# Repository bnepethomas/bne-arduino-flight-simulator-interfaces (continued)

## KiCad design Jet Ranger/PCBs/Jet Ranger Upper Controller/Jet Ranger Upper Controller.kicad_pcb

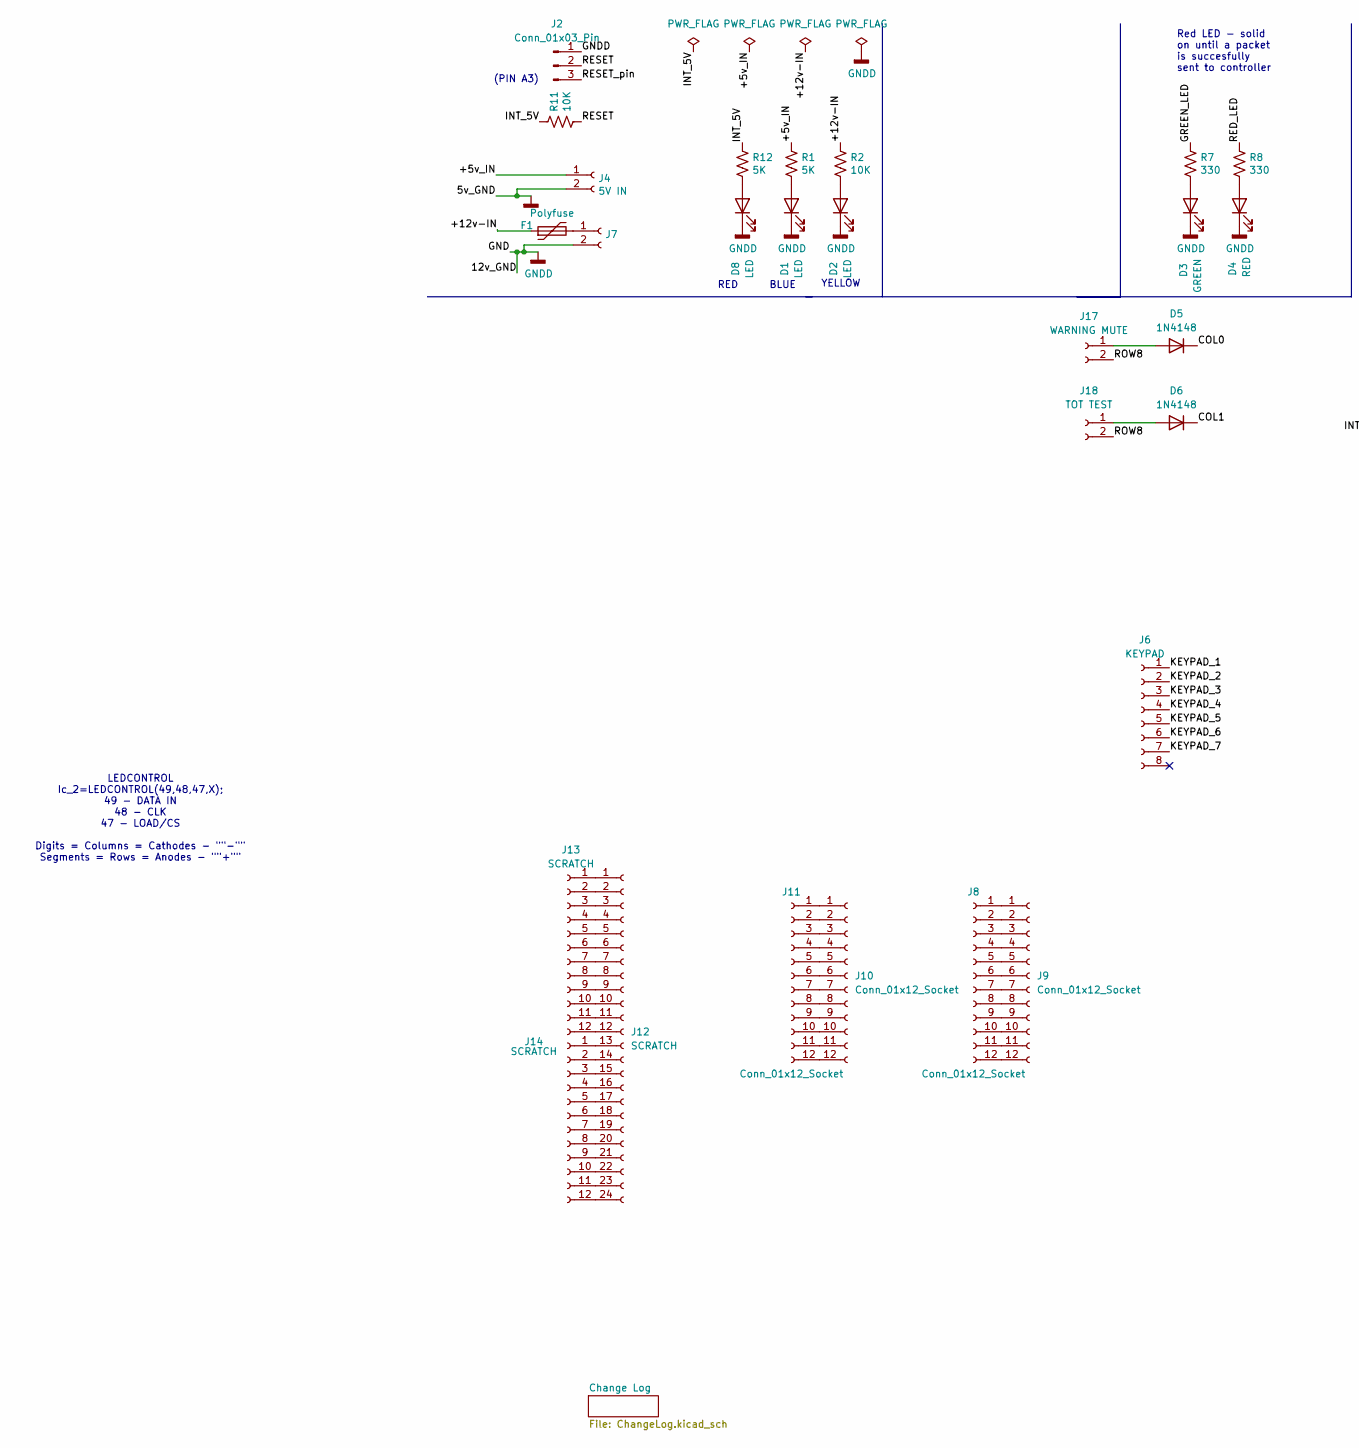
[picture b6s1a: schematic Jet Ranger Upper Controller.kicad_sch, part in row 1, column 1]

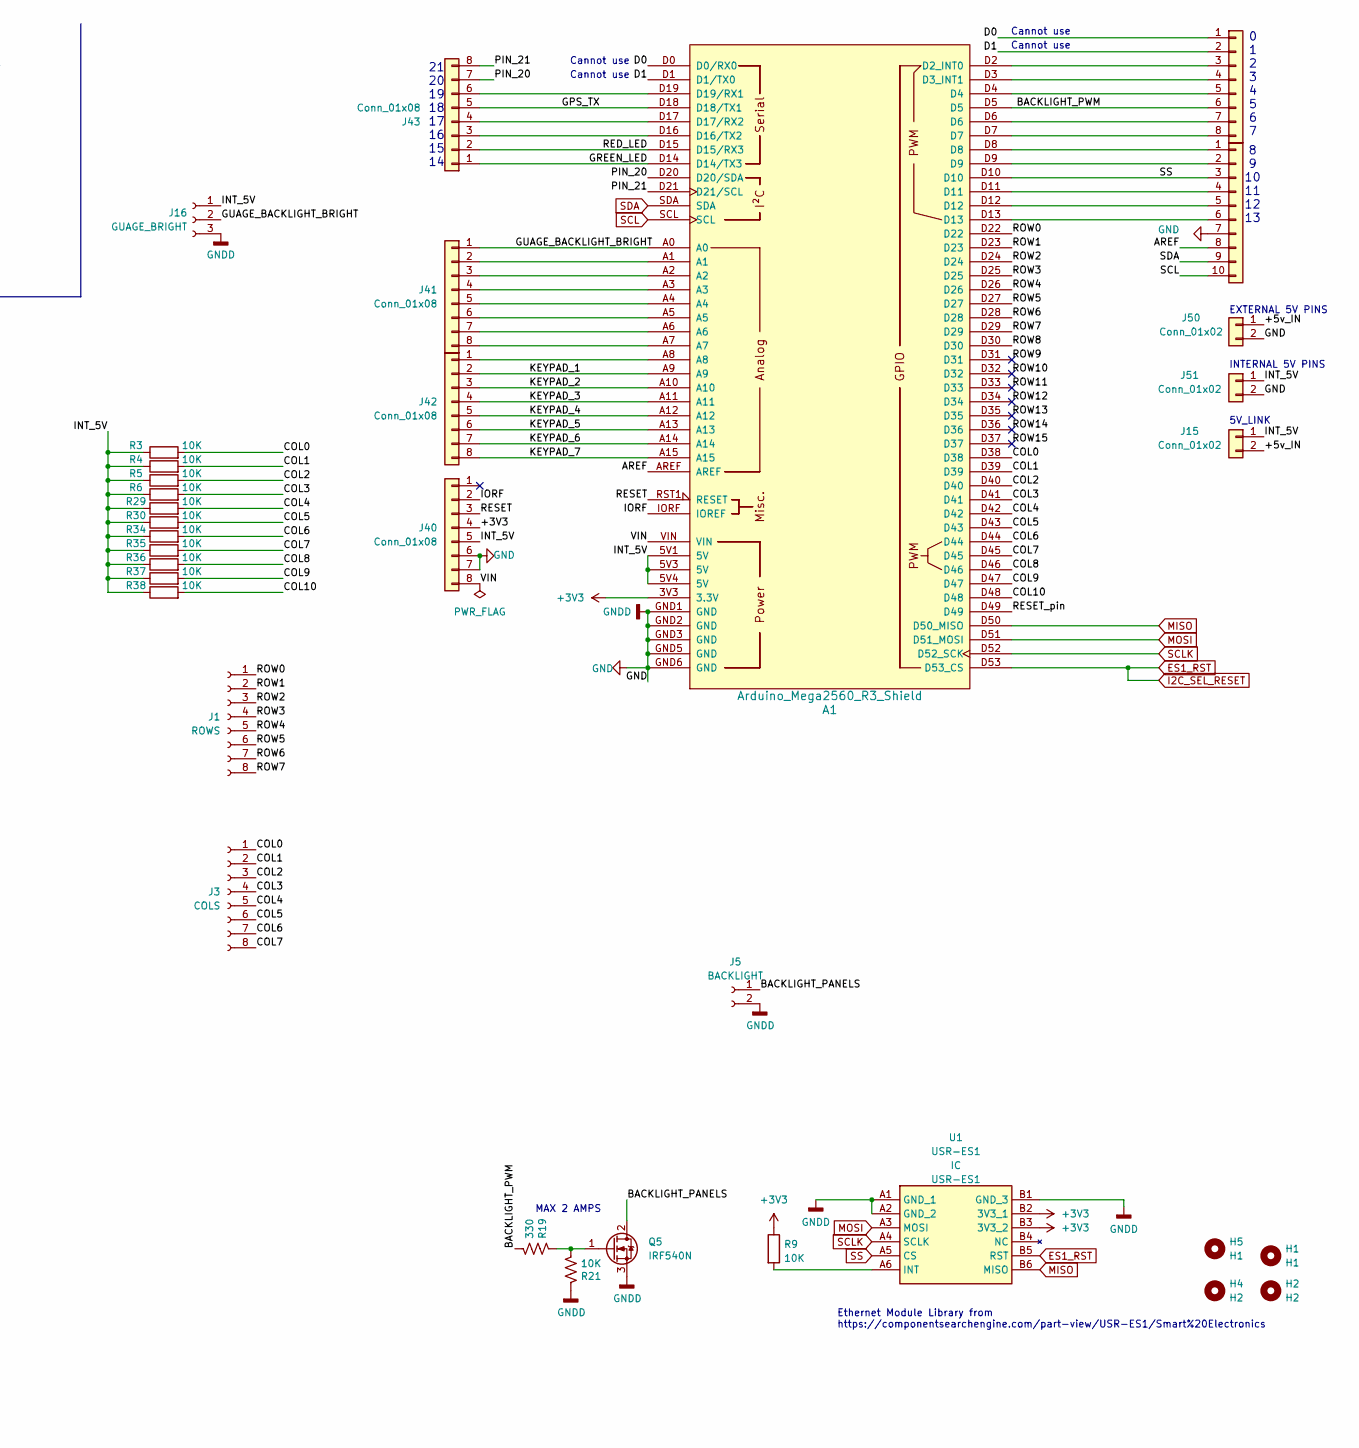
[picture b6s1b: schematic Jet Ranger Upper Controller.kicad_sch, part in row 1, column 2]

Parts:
A1: Arduino_Mega2560_R3_Shield
D1, D2, D8: LED; LED_D3.0mm
D3: GREEN; LED_D3.0mm
D4: RED; LED_D3.0mm
D5, D6: 1N4148; D_DO-35_SOD27_P7.62mm_Horizontal
F1: Polyfuse; Fuse_Bourns_MF-RG400
H1, H5: H1; MountingHole_3.2mm_M3
H2, H4: H2; MountingHole_3.2mm_M3
J1: ROWS; Molex_KK-254_AE-6410-08A_1x08_P2.54mm_Vertical
J2: Conn_01x03_Pin; PinHeader_1x03_P2.54mm_Vertical
J3: COLS; Molex_KK-254_AE-6410-08A_1x08_P2.54mm_Vertical
J4: 5V IN; BarrelJack_Horizontal
J5: BACKLIGHT; Molex_KK-254_AE-6410-02A_1x02_P2.54mm_Vertical
J6: KEYPAD; Molex_KK-254_AE-6410-08A_1x08_P2.54mm_Vertical
J7: STEPPER IN 12-20VDC; BarrelJack_Horizontal
J8, J9, J10, J11: Conn_01x12_Socket; PinHeader_1x12_P2.54mm_Vertical
J12: SCRATCH; IDC-Header_2x12_P2.54mm_Vertical
J13, J14: SCRATCH; PinHeader_1x12_P2.54mm_Vertical
J15, J50, J51: Conn_01x02; PinHeader_1x02_P2.54mm_Vertical
J16: GUAGE_BRIGHT; Molex_KK-254_AE-6410-03A_1x03_P2.54mm_Vertical
J17: WARNING MUTE; Molex_KK-254_AE-6410-02A_1x02_P2.54mm_Vertical
J18: TOT TEST; Molex_KK-254_AE-6410-02A_1x02_P2.54mm_Vertical
J40, J41, J42, J43, J44: Conn_01x08; PinHeader_1x08_P2.54mm_Vertical
J45: Conn_01x10; PinHeader_1x10_P2.54mm_Vertical
Q5: IRF540N; TO-220-3_Vertical
R1, R12: 5K; R_Axial_DIN0207_L6.3mm_D2.5mm_P2.54mm_Vertical
R2, R3, R4, R5, R6, R9, R11, R21, R29, R30, R34, R35, R36, R37, R38: 10K; R_Axial_DIN0207_L6.3mm_D2.5mm_P2.54mm_Vertical
R7, R8, R19: 330; R_Axial_DIN0207_L6.3mm_D2.5mm_P2.54mm_Vertical
U1: USR-ES1; USRES1; Manufacturer_Part_Number USR-ES1

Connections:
+3V3: A1.3V3 (3.3V), J40.4, R9.1, U1.B2 (3V3_1), U1.B3 (3V3_2)
/+5v_IN: J4.1, J15.2, J50.1, R1.1
/+12v-IN: F1.1, R2.1
/AREF: A1.AREF, J45.8
/BACKLIGHT_PANELS: J5.1, Q5.2 (D)
/BACKLIGHT_PWM: A1.D5, J44.6, R19.2
/COL0: A1.D38, D5.1 (K), J3.1, R3.2
/COL1: A1.D39, D6.1 (K), J3.2, R4.2
/COL2: A1.D40, J3.3, R5.2
/COL3: A1.D41, J3.4, R6.2
/COL4: A1.D42, J3.5, R29.2
/COL5: A1.D43, J3.6, R30.2
/COL6: A1.D44, J3.7, R34.2
/COL7: A1.D45, J3.8, R35.2
/COL8: A1.D46, R36.2
/COL9: A1.D47, R37.2
/COL10: A1.D48, R38.2
/D0: A1.D0 (D0/RX0), J44.1
/D1: A1.D1 (D1/TX0), J44.2
/GPS_TX: A1.D18 (D18/TX1), J43.5
/GREEN_LED: A1.D14 (D14/TX3), J43.1, R7.1
/GUAGE_BACKLIGHT_BRIGHT: A1.A0, J16.2, J41.1
/INT_5V: A1.5V1 (5V), A1.5V3 (5V), A1.5V4 (5V), J15.1, J16.1, J40.5, J51.1, R3.1, R4.1, R5.1, R6.1, R11.1, R12.1, R29.1, R30.1, R34.1, R35.1, R36.1, R37.1, R38.1
/IORF: A1.IORF (IOREF), J40.2
/KEYPAD_1: A1.A9, J6.1, J42.2
/KEYPAD_2: A1.A10, J6.2, J42.3
/KEYPAD_3: A1.A11, J6.3, J42.4
/KEYPAD_4: A1.A12, J6.4, J42.5
/KEYPAD_5: A1.A13, J6.5, J42.6
/KEYPAD_6: A1.A14, J6.6, J42.7
/KEYPAD_7: A1.A15, J6.7, J42.8
/PIN_20: A1.D20 (D20/SDA), J43.7
/PIN_21: A1.D21 (D21/SCL), J43.8
/RED_LED: A1.D15 (D15/RX3), J43.2, R8.1
/RESET: A1.RST1 (RESET), J2.2, J40.3, R11.2
/RESET_pin: A1.D49, J2.3
/ROW0: A1.D22, J1.1
/ROW1: A1.D23, J1.2
/ROW2: A1.D24, J1.3
/ROW3: A1.D25, J1.4
/ROW4: A1.D26, J1.5
/ROW5: A1.D27, J1.6
/ROW6: A1.D28, J1.7
/ROW7: A1.D29, J1.8
/ROW8: A1.D30, J17.2, J18.2
/ROW9: A1.D31
/ROW10: A1.D32
/ROW11: A1.D33
/ROW12: A1.D34
/ROW13: A1.D35
/ROW14: A1.D36
/ROW15: A1.D37
/VIN: A1.VIN, J40.8
ES1_RST: A1.D53 (D53_CS), U1.B5 (RST)
GND: A1.GND1 (GND), A1.GND2 (GND), A1.GND3 (GND), A1.GND5 (GND), A1.GND6 (GND), D1.1 (K), D2.1 (K), D3.1 (K), D4.1 (K), D8.1 (K), J2.1, J4.2, J5.2, J7.2, J16.3, J40.6, J40.7, J45.7, J50.2, J51.2, Q5.3 (S), R21.1, U1.A1 (GND_1), U1.A2 (GND_2), U1.B1 (GND_3)
MISO: A1.D50 (D50_MISO), U1.B6 (MISO)
MOSI: A1.D51 (D51_MOSI), U1.A3 (MOSI)
unnamed: A1.D2 (D2_INT0), J44.3
unnamed: A1.D3 (D3_INT1), J44.4
unnamed: A1.D16 (D16/TX2), J43.3
unnamed: A1.D17 (D17/RX2), J43.4
unnamed: A1.D19 (D19/RX1), J43.6
unnamed: D1.2 (A), R1.2
unnamed: D2.2 (A), R2.2
unnamed: D3.2 (A), R7.2
unnamed: D4.2 (A), R8.2
unnamed: D5.2 (A), J17.1
unnamed: D6.2 (A), J18.1
unnamed: D8.2 (A), R12.2
unnamed: F1.2, J7.1
unnamed: J8.1, J9.1
unnamed: J8.2, J9.2
unnamed: J8.3, J9.3
unnamed: J8.4, J9.4
unnamed: J8.5, J9.5
unnamed: J8.6, J9.6
unnamed: J8.7, J9.7
unnamed: J8.8, J9.8
unnamed: J8.9, J9.9
unnamed: J8.10, J9.10
unnamed: J8.11, J9.11
unnamed: J8.12, J9.12
unnamed: J10.1, J11.1
unnamed: J10.2, J11.2
unnamed: J10.3, J11.3
unnamed: J10.4, J11.4
unnamed: J10.5, J11.5
unnamed: J10.6, J11.6
unnamed: J10.7, J11.7
unnamed: J10.8, J11.8
unnamed: J10.9, J11.9
unnamed: J10.10, J11.10
unnamed: J10.11, J11.11
unnamed: J10.12, J11.12
unnamed: J12.1, J13.1
unnamed: J12.2, J13.2
unnamed: J12.3, J13.3
unnamed: J12.4, J13.4
unnamed: J12.5, J13.5
unnamed: J12.6, J13.6
unnamed: J12.7, J13.7
unnamed: J12.8, J13.8
unnamed: J12.9, J13.9
unnamed: J12.10, J13.10
unnamed: J12.11, J13.11
unnamed: J12.12, J13.12
unnamed: J12.13, J14.1
unnamed: J12.14, J14.2
unnamed: J12.15, J14.3
unnamed: J12.16, J14.4
unnamed: J12.17, J14.5
unnamed: J12.18, J14.6
unnamed: J12.19, J14.7
unnamed: J12.20, J14.8
unnamed: J12.21, J14.9
unnamed: J12.22, J14.10
unnamed: J12.23, J14.11
unnamed: J12.24, J14.12
unnamed: A1.A1, J41.2
unnamed: A1.A2, J41.3
unnamed: A1.A3, J41.4
unnamed: A1.A4, J41.5
unnamed: A1.A5, J41.6
unnamed: A1.A6, J41.7
unnamed: A1.A7, J41.8
unnamed: A1.A8, J42.1
unnamed: A1.D4, J44.5
unnamed: A1.D6, J44.7
unnamed: A1.D7, J44.8
unnamed: A1.D8, J45.1
unnamed: A1.D9, J45.2
unnamed: A1.D11, J45.4
unnamed: A1.D12, J45.5
unnamed: A1.D13, J45.6
unnamed: Q5.1 (G), R19.1, R21.2
unnamed: R9.2, U1.A6 (INT)
SCL: A1.SCL, J45.10
SCLK: A1.D52 (D52_SCK), U1.A4 (SCLK)
SDA: A1.SDA, J45.9
SS: A1.D10, J45.3, U1.A5 (CS)

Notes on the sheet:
YELLOW
MAX 2 AMPS
BLUE
INTERNAL 5V PINS
Ethernet Module Library from https://componentsearchengine.com/part-view/USR-ES1/Smart%20Electronics
Cannot use
RED
(PIN A3)
0 1 2 3 4 5 6 7
LEDCONTROL Ic_2=LEDCONTROL(49,48,47,X); 49 - DATA IN 48 - CLK 47 - LOAD/CS Digits = Columns = Cathodes - ""-"" Segments = Rows = Anodes - ""+""
Red LED - solid on until a packet is succesfully sent to controller
5V_LINK
21 20 19 18 17 16 15 14
EXTERNAL 5V PINS
8 9 10 11 12 13

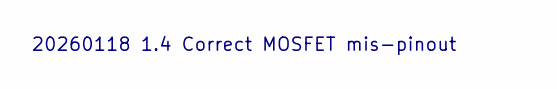
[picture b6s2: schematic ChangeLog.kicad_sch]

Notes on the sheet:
20260118 1.4 Correct MOSFET mis-pinout

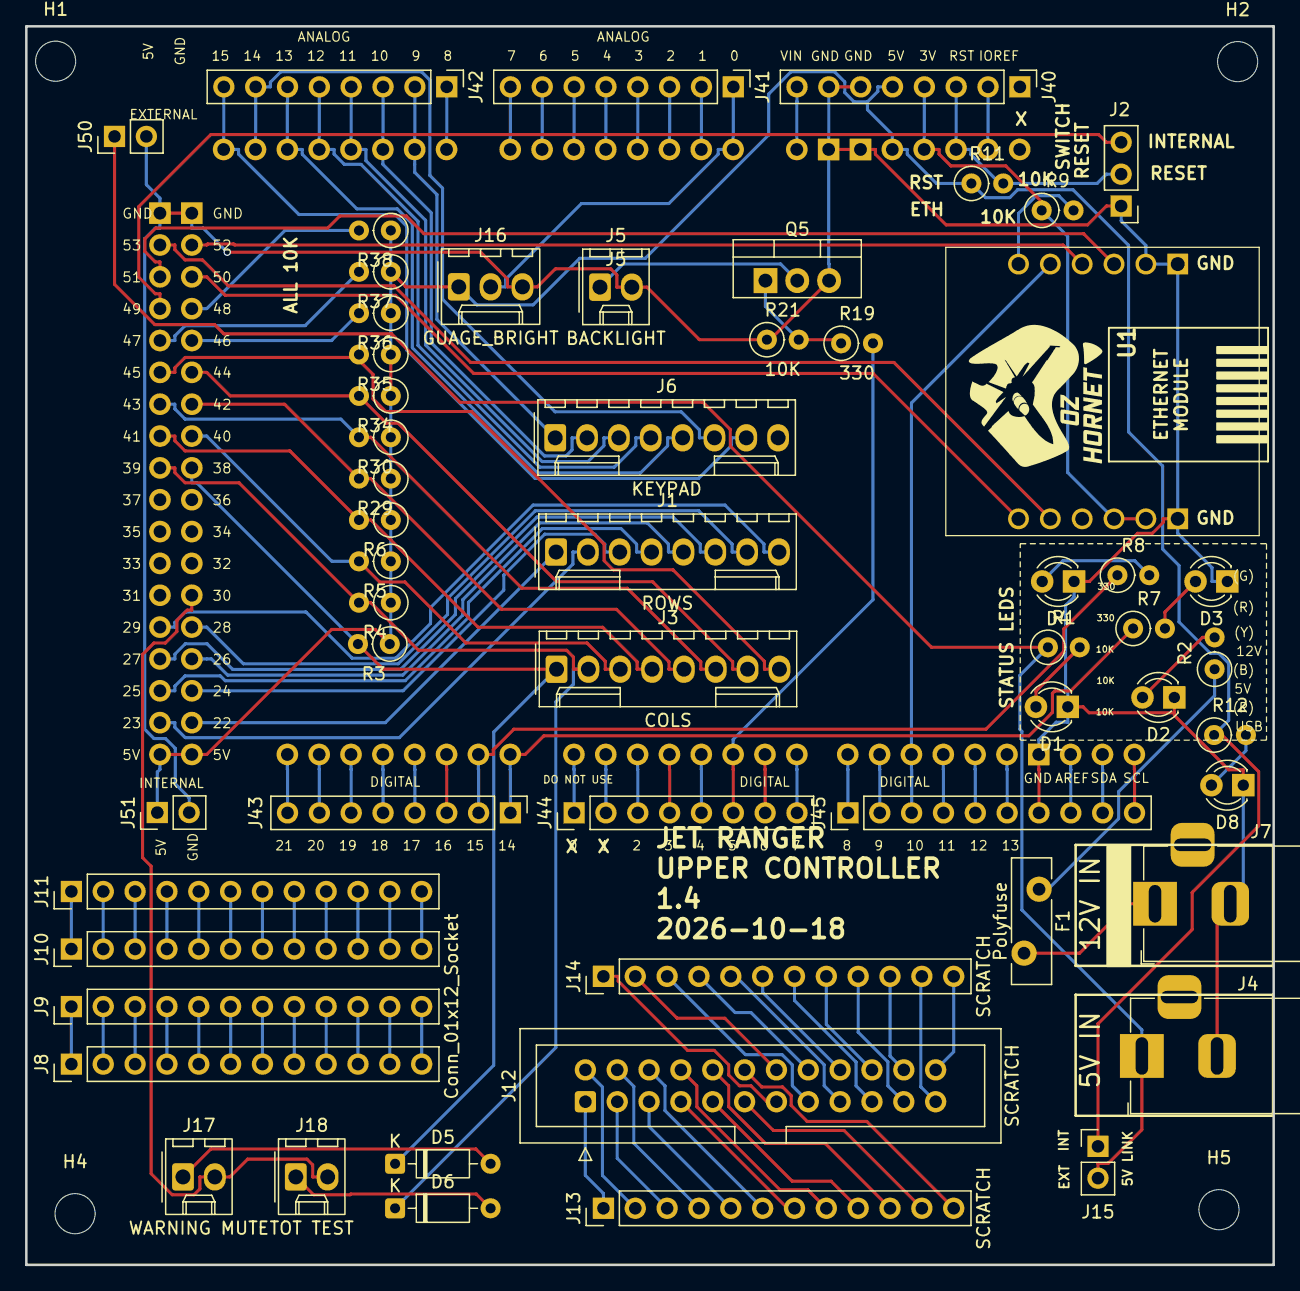
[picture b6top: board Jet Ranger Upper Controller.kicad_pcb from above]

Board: 2 copper layers, 99.5 x 98.8 mm, 61 parts (0 on the bottom side), 133 nets.

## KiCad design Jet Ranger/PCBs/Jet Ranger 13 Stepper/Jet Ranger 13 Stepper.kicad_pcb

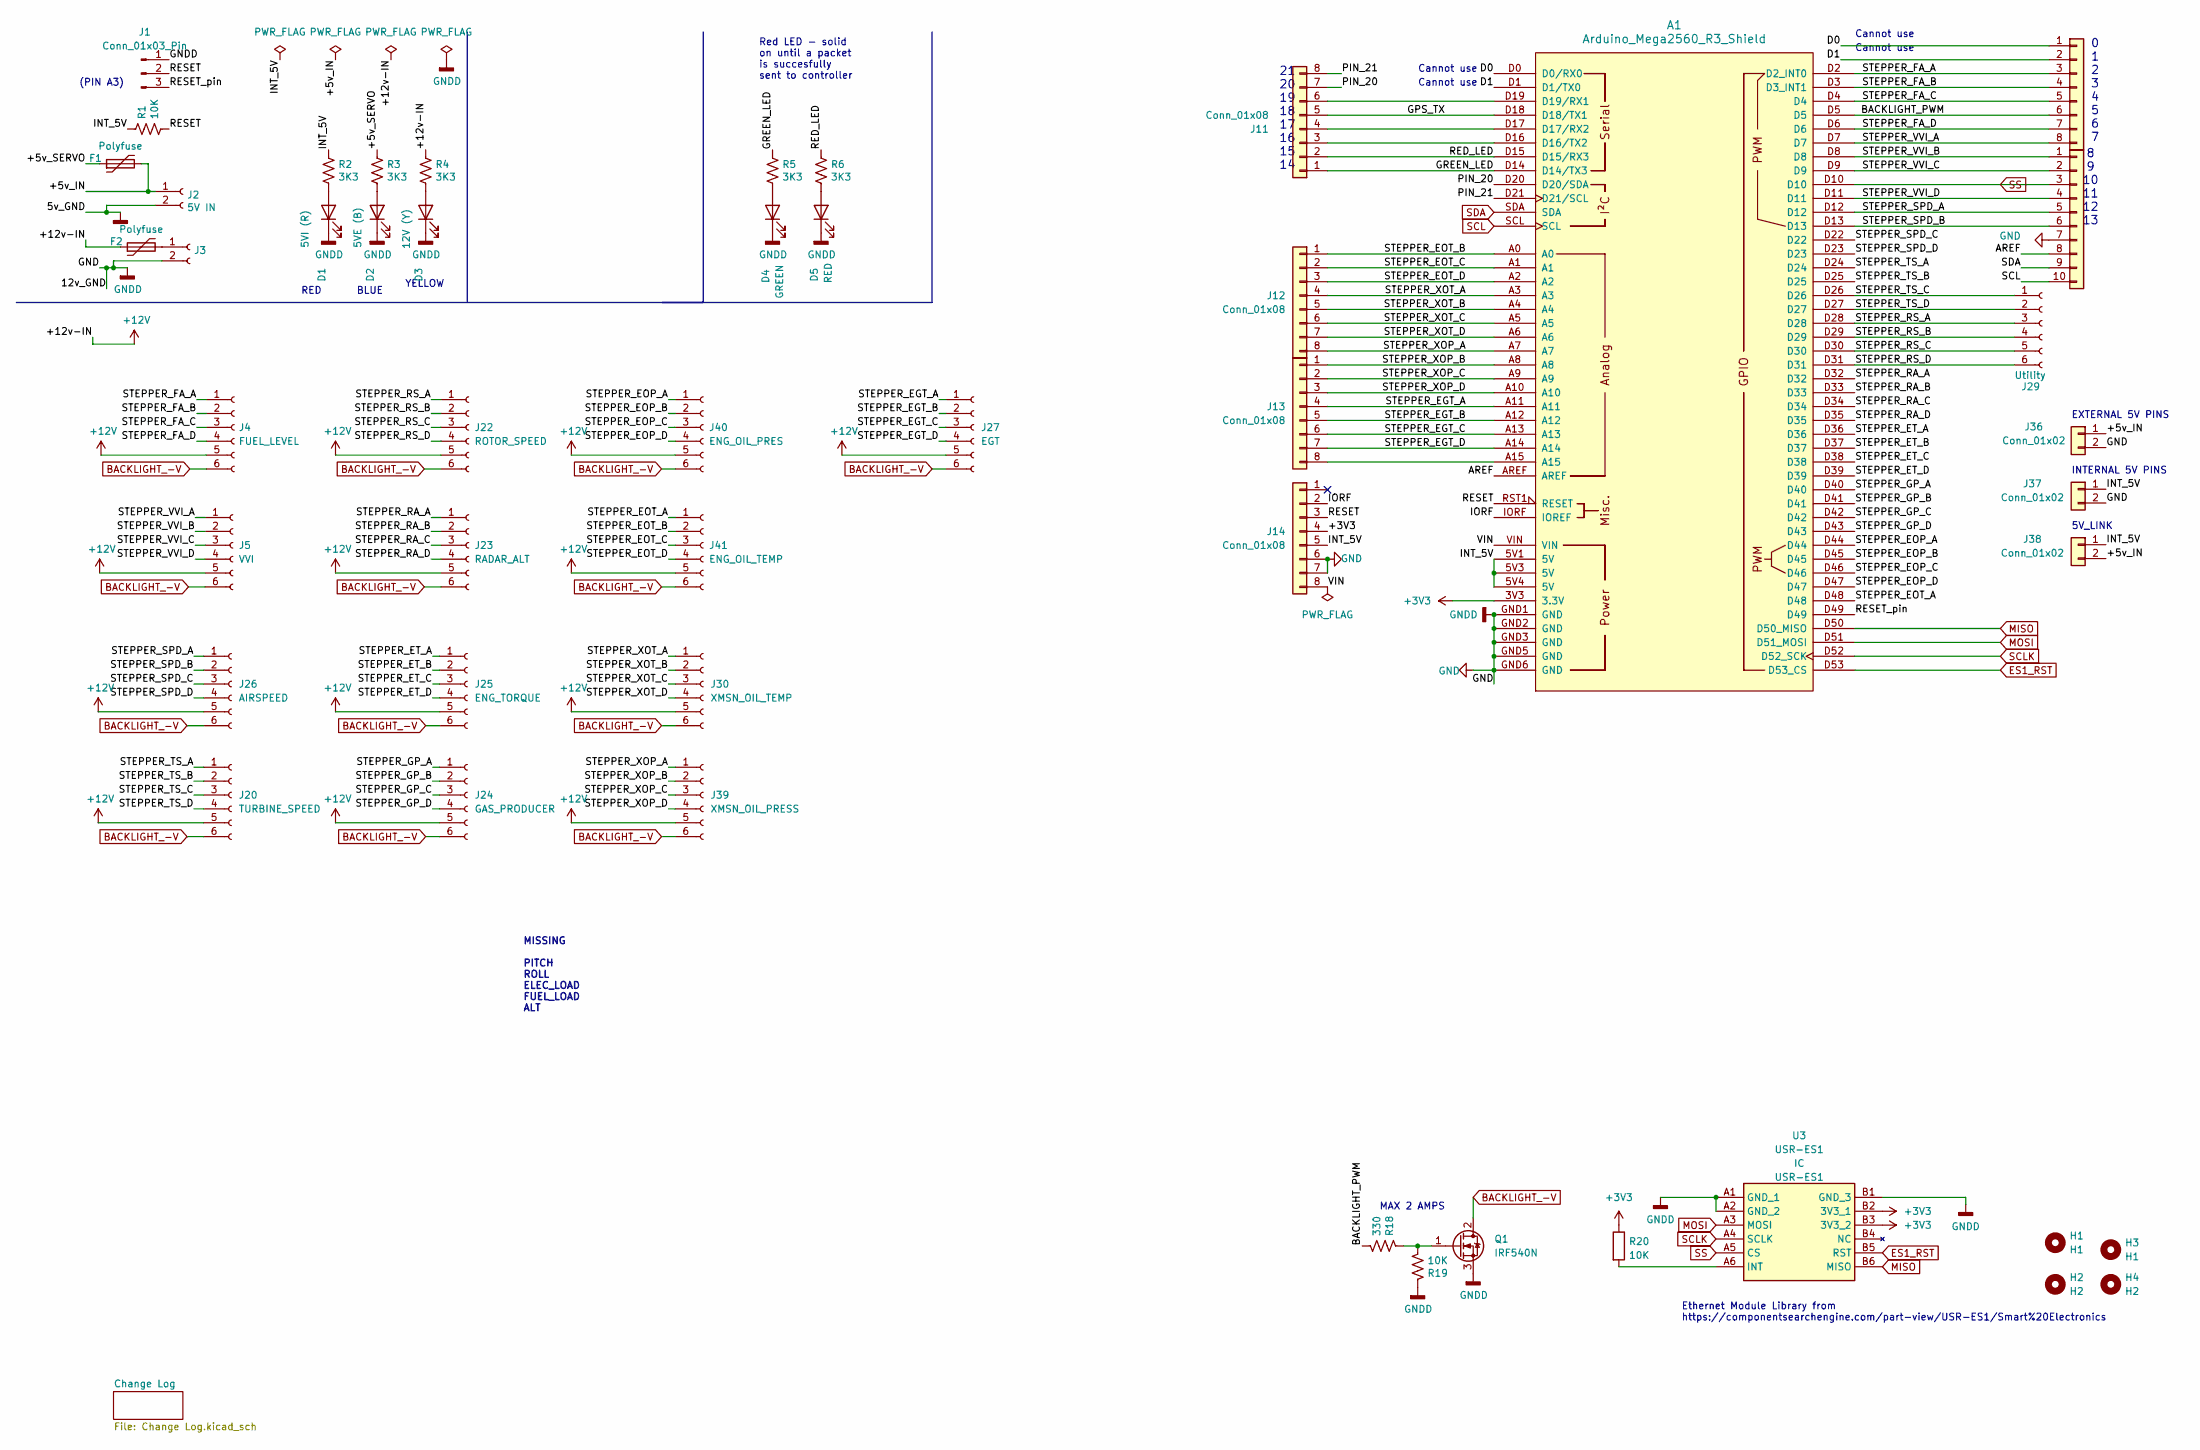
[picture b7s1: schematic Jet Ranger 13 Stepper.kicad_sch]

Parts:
A1: Arduino_Mega2560_R3_Shield
D1: 5VI (R); LED_D3.0mm
D2: 5VE (B); LED_D3.0mm
D3: 12V (Y); LED_D3.0mm
D4: GREEN; LED_D3.0mm
D5: RED; LED_D3.0mm
F1, F2: Polyfuse; Fuse_Littelfuse_395Series
H1, H3: H1; MountingHole_3.2mm_M3
H2, H4: H2; MountingHole_3.2mm_M3
J1: Conn_01x03_Pin; PinHeader_1x03_P2.54mm_Vertical
J2: 5V IN; BarrelJack_Horizontal
J3: STEPPER IN 12-20VDC; BarrelJack_Horizontal
J4: FUEL_LEVEL; Molex_KK-254_AE-6410-06A_1x06_P2.54mm_Vertical
J5: VVI; Molex_KK-254_AE-6410-06A_1x06_P2.54mm_Vertical
J11, J12, J13, J14, J34: Conn_01x08; PinHeader_1x08_P2.54mm_Vertical
J20: TURBINE_SPEED; Molex_KK-254_AE-6410-06A_1x06_P2.54mm_Vertical
J22: ROTOR_SPEED; Molex_KK-254_AE-6410-06A_1x06_P2.54mm_Vertical
J23: RADAR_ALT; Molex_KK-254_AE-6410-06A_1x06_P2.54mm_Vertical
J24: GAS_PRODUCER; Molex_KK-254_AE-6410-06A_1x06_P2.54mm_Vertical
J25: ENG_TORQUE; Molex_KK-254_AE-6410-06A_1x06_P2.54mm_Vertical
J26: AIRSPEED; Molex_KK-254_AE-6410-06A_1x06_P2.54mm_Vertical
J27: EGT; Molex_KK-254_AE-6410-06A_1x06_P2.54mm_Vertical
J29: Utility; PinHeader_1x06_P2.54mm_Vertical
J30: XMSN_OIL_TEMP; Molex_KK-254_AE-6410-06A_1x06_P2.54mm_Vertical
J35: Conn_01x10; PinHeader_1x10_P2.54mm_Vertical
J36, J37, J38: Conn_01x02; PinHeader_1x02_P2.54mm_Vertical
J39: XMSN_OIL_PRESS; Molex_KK-254_AE-6410-06A_1x06_P2.54mm_Vertical
J40: ENG_OIL_PRES; Molex_KK-254_AE-6410-06A_1x06_P2.54mm_Vertical
J41: ENG_OIL_TEMP; Molex_KK-254_AE-6410-06A_1x06_P2.54mm_Vertical
Q1: IRF540N; TO-220-3_Vertical
R1, R19, R20: 10K; R_Axial_DIN0207_L6.3mm_D2.5mm_P2.54mm_Vertical
R2, R3, R4, R5, R6: 3K3; R_Axial_DIN0207_L6.3mm_D2.5mm_P2.54mm_Vertical
R18: 330; R_Axial_DIN0207_L6.3mm_D2.5mm_P2.54mm_Vertical
U3: USR-ES1; USRES1; Manufacturer_Part_Number USR-ES1

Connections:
+3V3: A1.3V3 (3.3V), J14.4, R20.1, U3.B2 (3V3_1), U3.B3 (3V3_2)
+12V: F2.1, J4.5, J5.5, J20.5, J22.5, J23.5, J24.5, J25.5, J26.5, J27.5, J30.5, J39.5, J40.5, J41.5, R4.1
/+5v_IN: F1.2, J2.1, J36.1, J38.2
/+5v_SERVO: F1.1, R3.1
/AREF: A1.AREF, J35.8
/BACKLIGHT_PWM: A1.D5, J34.6, R18.2
/D0: A1.D0 (D0/RX0), J34.1
/D1: A1.D1 (D1/TX0), J34.2
/GPS_TX: A1.D18 (D18/TX1), J11.5
/GREEN_LED: A1.D14 (D14/TX3), J11.1, R5.1
/INT_5V: A1.5V1 (5V), A1.5V3 (5V), A1.5V4 (5V), J14.5, J37.1, J38.1, R1.1, R2.1
/IORF: A1.IORF (IOREF), J14.2
/PIN_20: A1.D20 (D20/SDA), J11.7
/PIN_21: A1.D21 (D21/SCL), J11.8
/RED_LED: A1.D15 (D15/RX3), J11.2, R6.1
/RESET: A1.RST1 (RESET), J1.2, J14.3, R1.2
/RESET_pin: A1.D49, J1.3
/STEPPER_EGT_A: A1.A11, J13.4, J27.1
/STEPPER_EGT_B: A1.A12, J13.5, J27.2
/STEPPER_EGT_C: A1.A13, J13.6, J27.3
/STEPPER_EGT_D: A1.A14, J13.7, J27.4
/STEPPER_EOP_A: A1.D44, J40.1
/STEPPER_EOP_B: A1.D45, J40.2
/STEPPER_EOP_C: A1.D46, J40.3
/STEPPER_EOP_D: A1.D47, J40.4
/STEPPER_EOT_A: A1.D48, J41.1
/STEPPER_EOT_B: A1.A0, J12.1, J41.2
/STEPPER_EOT_C: A1.A1, J12.2, J41.3
/STEPPER_EOT_D: A1.A2, J12.3, J41.4
/STEPPER_ET_A: A1.D36, J25.1
/STEPPER_ET_B: A1.D37, J25.2
/STEPPER_ET_C: A1.D38, J25.3
/STEPPER_ET_D: A1.D39, J25.4
/STEPPER_FA_A: A1.D2 (D2_INT0), J4.1, J34.3
/STEPPER_FA_B: A1.D3 (D3_INT1), J4.2, J34.4
/STEPPER_FA_C: A1.D4, J4.3, J34.5
/STEPPER_FA_D: A1.D6, J4.4, J34.7
/STEPPER_GP_A: A1.D40, J24.1
/STEPPER_GP_B: A1.D41, J24.2
/STEPPER_GP_C: A1.D42, J24.3
/STEPPER_GP_D: A1.D43, J24.4
/STEPPER_RA_A: A1.D32, J23.1
/STEPPER_RA_B: A1.D33, J23.2
/STEPPER_RA_C: A1.D34, J23.3
/STEPPER_RA_D: A1.D35, J23.4
/STEPPER_RS_A: A1.D28, J22.1, J29.3
/STEPPER_RS_B: A1.D29, J22.2, J29.4
/STEPPER_RS_C: A1.D30, J22.3, J29.5
/STEPPER_RS_D: A1.D31, J22.4, J29.6
/STEPPER_SPD_A: A1.D12, J26.1, J35.5
/STEPPER_SPD_B: A1.D13, J26.2, J35.6
/STEPPER_SPD_C: A1.D22, J26.3
/STEPPER_SPD_D: A1.D23, J26.4
/STEPPER_TS_A: A1.D24, J20.1
/STEPPER_TS_B: A1.D25, J20.2
/STEPPER_TS_C: A1.D26, J20.3, J29.1
/STEPPER_TS_D: A1.D27, J20.4, J29.2
/STEPPER_VVI_A: A1.D7, J5.1, J34.8
/STEPPER_VVI_B: A1.D8, J5.2, J35.1
/STEPPER_VVI_C: A1.D9, J5.3, J35.2
/STEPPER_VVI_D: A1.D11, J5.4, J35.4
/STEPPER_XOP_A: A1.A7, J12.8, J39.1
/STEPPER_XOP_B: A1.A8, J13.1, J39.2
/STEPPER_XOP_C: A1.A9, J13.2, J39.3
/STEPPER_XOP_D: A1.A10, J13.3, J39.4
/STEPPER_XOT_A: A1.A3, J12.4, J30.1
/STEPPER_XOT_B: A1.A4, J12.5, J30.2
/STEPPER_XOT_C: A1.A5, J12.6, J30.3
/STEPPER_XOT_D: A1.A6, J12.7, J30.4
/VIN: A1.VIN, J14.8
BACKLIGHT_-V: J4.6, J5.6, J20.6, J22.6, J23.6, J24.6, J25.6, J26.6, J27.6, J30.6, J39.6, J40.6, J41.6, Q1.2 (D)
ES1_RST: A1.D53 (D53_CS), U3.B5 (RST)
GND: A1.GND1 (GND), A1.GND2 (GND), A1.GND3 (GND), A1.GND5 (GND), A1.GND6 (GND), D1.1 (K), D2.1 (K), D3.1 (K), D4.1 (K), D5.1 (K), J1.1, J2.2, J3.2, J14.6, J14.7, J35.7, J36.2, J37.2, Q1.3 (S), R19.1, U3.A1 (GND_1), U3.A2 (GND_2), U3.B1 (GND_3)
MISO: A1.D50 (D50_MISO), U3.B6 (MISO)
MOSI: A1.D51 (D51_MOSI), U3.A3 (MOSI)
unnamed: A1.D16 (D16/TX2), J11.3
unnamed: A1.D17 (D17/RX2), J11.4
unnamed: A1.D19 (D19/RX1), J11.6
unnamed: D1.2 (A), R2.2
unnamed: D2.2 (A), R3.2
unnamed: D3.2 (A), R4.2
unnamed: D4.2 (A), R5.2
unnamed: D5.2 (A), R6.2
unnamed: F2.2, J3.1
unnamed: A1.A15, J13.8
unnamed: Q1.1 (G), R18.1, R19.2
unnamed: R20.2, U3.A6 (INT)
SCL: A1.SCL, J35.10
SCLK: A1.D52 (D52_SCK), U3.A4 (SCLK)
SDA: A1.SDA, J35.9
SS: A1.D10, J35.3, U3.A5 (CS)

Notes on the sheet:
YELLOW
MAX 2 AMPS
MISSING PITCH ROLL ELEC_LOAD FUEL_LOAD ALT
BLUE
INTERNAL 5V PINS
Ethernet Module Library from https://componentsearchengine.com/part-view/USR-ES1/Smart%20Electronics
Cannot use
RED
(PIN A3)
0 1 2 3 4 5 6 7
Red LED - solid on until a packet is succesfully sent to controller
5V_LINK
21 20 19 18 17 16 15 14
EXTERNAL 5V PINS
8 9 10 11 12 13

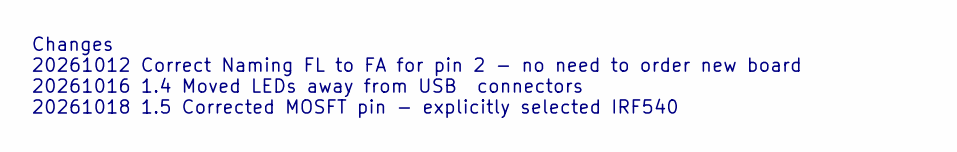
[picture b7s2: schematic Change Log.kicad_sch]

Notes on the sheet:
Changes 20261012 Correct Naming FL to FA for pin 2 - no need to order new board 20261016 1.4 Moved LEDs away from USB connectors 20261018 1.5 Corrected MOSFT pin - explicitly selected IRF540

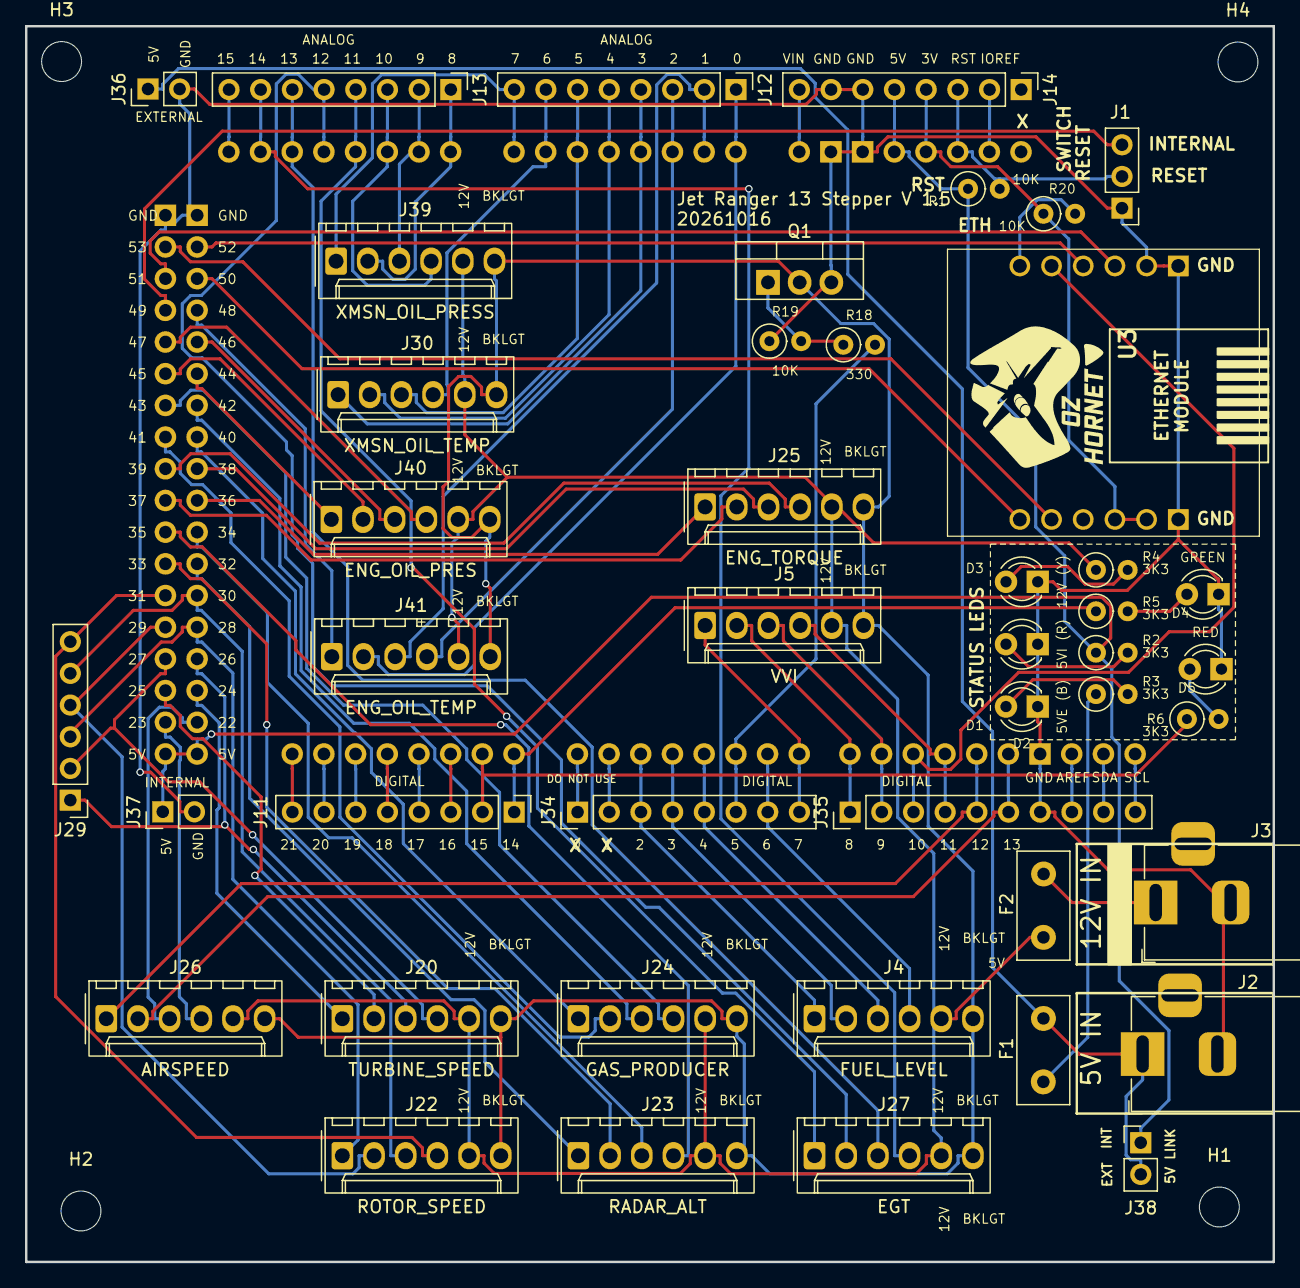
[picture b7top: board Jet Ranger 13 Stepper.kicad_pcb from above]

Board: 2 copper layers, 100.0 x 99.1 mm, 49 parts (0 on the bottom side), 91 nets.

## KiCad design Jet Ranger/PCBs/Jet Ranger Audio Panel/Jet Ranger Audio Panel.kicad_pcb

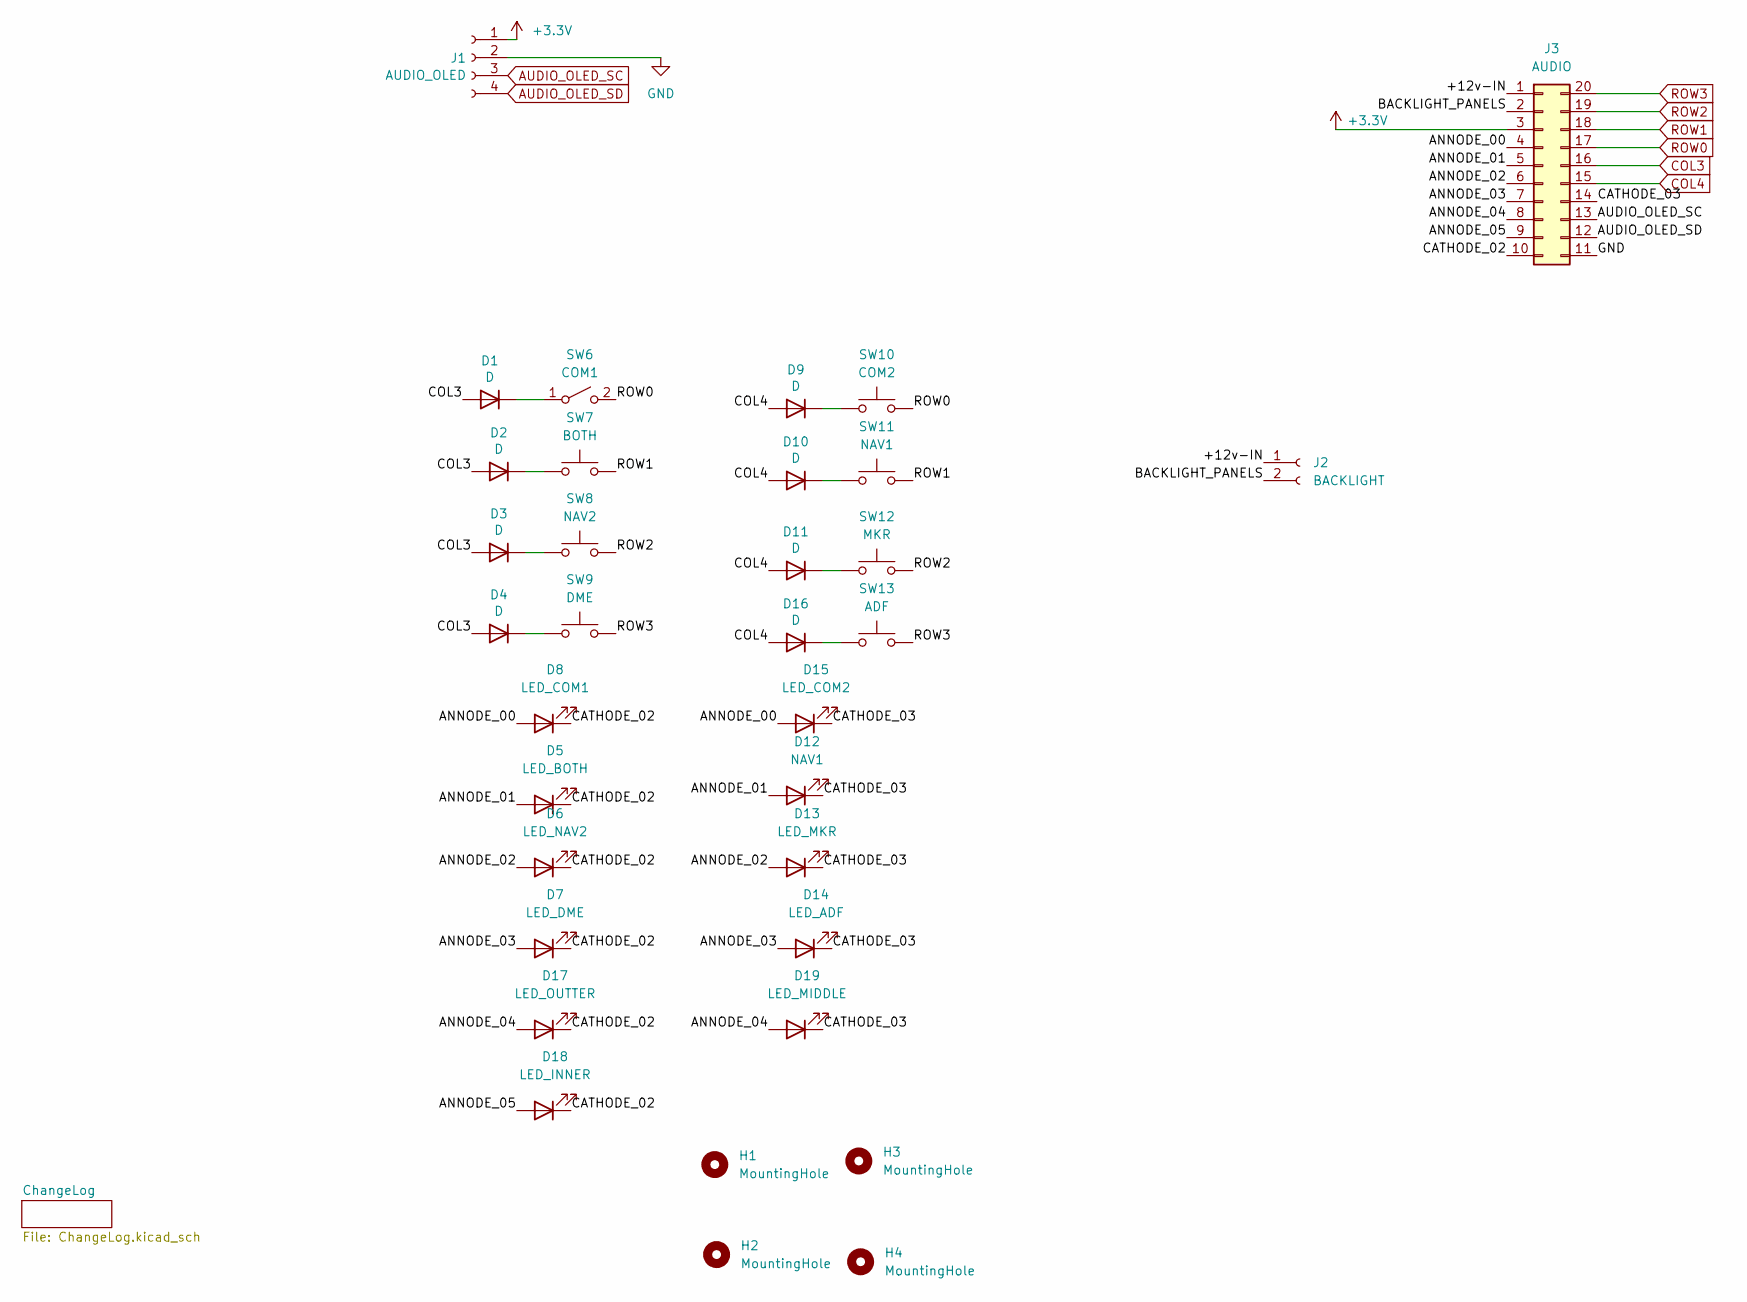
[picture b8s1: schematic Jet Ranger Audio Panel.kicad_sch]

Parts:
D1, D2, D3, D4, D9, D10, D11, D16: D; D_A-405_P7.62mm_Horizontal
D5: LED_BOTH; JST_XH_B2B-XH-A_1x02_P2.50mm_Vertical
D6: LED_NAV2; JST_XH_B2B-XH-A_1x02_P2.50mm_Vertical
D7: LED_DME; JST_XH_B2B-XH-A_1x02_P2.50mm_Vertical
D8: LED_COM1; JST_XH_B2B-XH-A_1x02_P2.50mm_Vertical
D12: NAV1; JST_XH_B2B-XH-A_1x02_P2.50mm_Vertical
D13: LED_MKR; JST_XH_B2B-XH-A_1x02_P2.50mm_Vertical
D14: LED_ADF; JST_XH_B2B-XH-A_1x02_P2.50mm_Vertical
D15: LED_COM2; JST_XH_B2B-XH-A_1x02_P2.50mm_Vertical
D17: LED_OUTTER; JST_XH_B2B-XH-A_1x02_P2.50mm_Vertical
D18: LED_INNER; JST_XH_B2B-XH-A_1x02_P2.50mm_Vertical
D19: LED_MIDDLE; JST_XH_B2B-XH-A_1x02_P2.50mm_Vertical
H1, H2, H3, H4: MountingHole; MountingHole_3.2mm_M3
J1: AUDIO_OLED; JST_XH_B4B-XH-A_1x04_P2.50mm_Vertical
J2: BACKLIGHT; JST_XH_B2B-XH-A_1x02_P2.50mm_Vertical
J3: AUDIO; IDC-Header_2x10_P2.54mm_Vertical
SW6: COM1; JST_XH_B2B-XH-A_1x02_P2.50mm_Vertical
SW7: BOTH; JST_XH_B2B-XH-A_1x02_P2.50mm_Vertical
SW8: NAV2; JST_XH_B2B-XH-A_1x02_P2.50mm_Vertical
SW9: DME; JST_XH_B2B-XH-A_1x02_P2.50mm_Vertical
SW10: COM2; JST_XH_B2B-XH-A_1x02_P2.50mm_Vertical
SW11: NAV1; JST_XH_B2B-XH-A_1x02_P2.50mm_Vertical
SW12: MKR; JST_XH_B2B-XH-A_1x02_P2.50mm_Vertical
SW13: ADF; JST_XH_B2B-XH-A_1x02_P2.50mm_Vertical

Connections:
+3.3V: J1.1, J3.3
/+12v-IN: J2.1, J3.1
/ANNODE_00: D8.1 (A), D15.1 (A), J3.4
/ANNODE_01: D5.1 (A), D12.1 (A), J3.5
/ANNODE_02: D6.1 (A), D13.1 (A), J3.6
/ANNODE_03: D7.1 (A), D14.1 (A), J3.7
/ANNODE_04: D17.1 (A), D19.1 (A), J3.8
/ANNODE_05: D18.1 (A), J3.9
/BACKLIGHT_PANELS: J2.2, J3.2
/CATHODE_02: D5.2 (K), D6.2 (K), D7.2 (K), D8.2 (K), D17.2 (K), D18.2 (K), J3.10
/CATHODE_03: D12.2 (K), D13.2 (K), D14.2 (K), D15.2 (K), D19.2 (K), J3.14
AUDIO_OLED_SC: J1.3, J3.13
AUDIO_OLED_SD: J1.4, J3.12
COL3: D1.2 (A), D2.2 (A), D3.2 (A), D4.2 (A), J3.16
COL4: D9.2 (A), D10.2 (A), D11.2 (A), D16.2 (A), J3.15
GND: J1.2, J3.11
unnamed: D1.1 (K), SW6.1 (A)
unnamed: D2.1 (K), SW7.1
unnamed: D3.1 (K), SW8.1
unnamed: D4.1 (K), SW9.1
unnamed: D9.1 (K), SW10.1
unnamed: D10.1 (K), SW11.1
unnamed: D11.1 (K), SW12.1
unnamed: D16.1 (K), SW13.1
ROW0: J3.17, SW6.2 (B), SW10.2
ROW1: J3.18, SW7.2, SW11.2
ROW2: J3.19, SW8.2, SW12.2
ROW3: J3.20, SW9.2, SW13.2

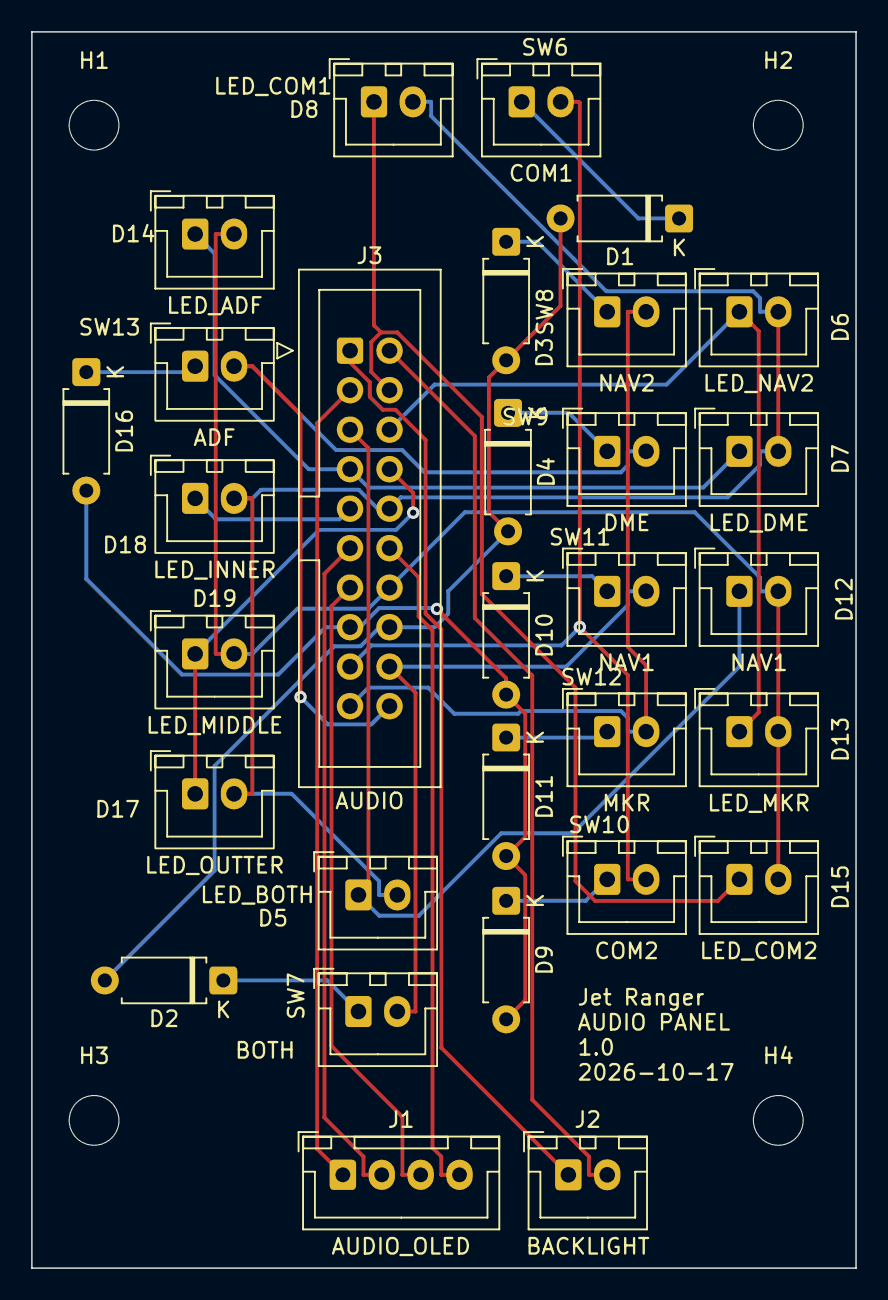
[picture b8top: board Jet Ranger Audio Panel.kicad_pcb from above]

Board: 2 copper layers, 53.0 x 79.5 mm, 34 parts (0 on the bottom side), 28 nets.
